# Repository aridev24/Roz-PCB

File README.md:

# Roz-PCB By AriDev24:

This is my first PCB, or you can also say my first ever hardware project that I ever made. In the beginning, I was scared to make it because it was so complex, but after some time It started to get fun. But that does not mean it got easier; it was still complex and gave me a headache. I never thought that I would be able to make a PCB as my first hardware project. 

## Features:

The following is a list of some features below: 

1. Glow-in-the-dark: whenever you take it into the darkness, the LEDs turn on, and its eyes start glowing, but in the light, the LEDs turn off.
2. You can put it in your room as a decoration so at night when you turn off the lights, it will turn on and look beautiful.
3. You can also attach it to your keychain, a great gift for a tech guy.

## Inspiration:

This PCB is highly inspired by a robot named Roz from the movie "The Wild Robot." I took a beautiful scene from the movie where the robot is holding a little duck and converted that into a PCB

## Components:
- 1x CR2032 battery holder
- 2x 5mm LED
- 2x 2N3904 NPN transistor
- 1x Photoresistor (LDR)
- 2x 470Ω resistor
- 1x 4.7kΩ resistor
- 1x 47kΩ resistor

## 3D View: 

## schematic:

## PCB:

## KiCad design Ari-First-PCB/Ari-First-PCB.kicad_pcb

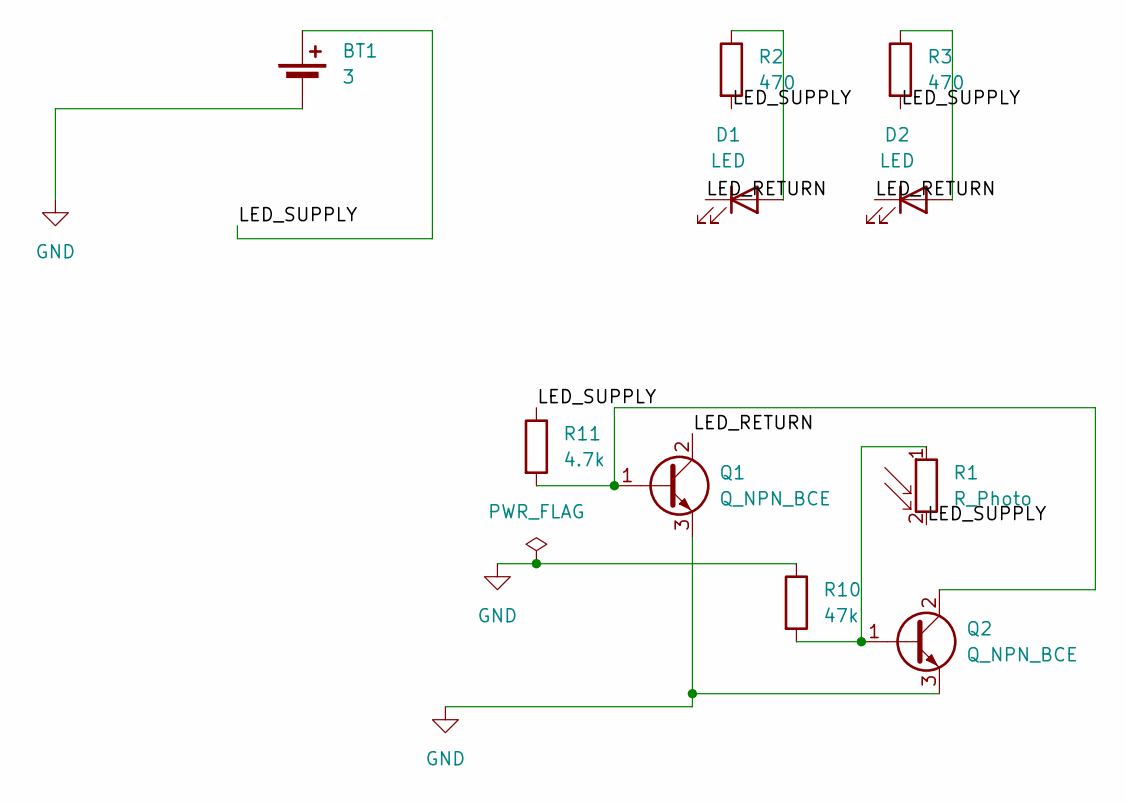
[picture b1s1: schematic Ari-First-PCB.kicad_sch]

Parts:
BT1: 3; BatteryHolder_Keystone_3034_1x20mm
D1, D2: LED; LED_D5.0mm
Q1, Q2: Q_NPN_BCE; TO-92L_HandSolder
R1: R_Photo; R_LDR_5.1x4.3mm_P3.4mm_Vertical
R2, R3: 470; R_Axial_DIN0207_L6.3mm_D2.5mm_P7.62mm_Horizontal
R10: 47k; R_Axial_DIN0207_L6.3mm_D2.5mm_P7.62mm_Horizontal
R11: 4.7k; R_Axial_DIN0207_L6.3mm_D2.5mm_P7.62mm_Horizontal

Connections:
/LED_RETURN: D1.1 (K), D2.1 (K), Q1.2 (C)
/LED_SUPPLY: BT1.1 (+), R1.2, R2.2, R3.2, R11.1
GND: BT1.2 (-), Q1.3 (E), Q2.3 (E), R10.1
unnamed: D1.2 (A), R2.1
unnamed: D2.2 (A), R3.1
unnamed: Q1.1 (B), Q2.2 (C), R11.2
unnamed: Q2.1 (B), R1.1, R10.2

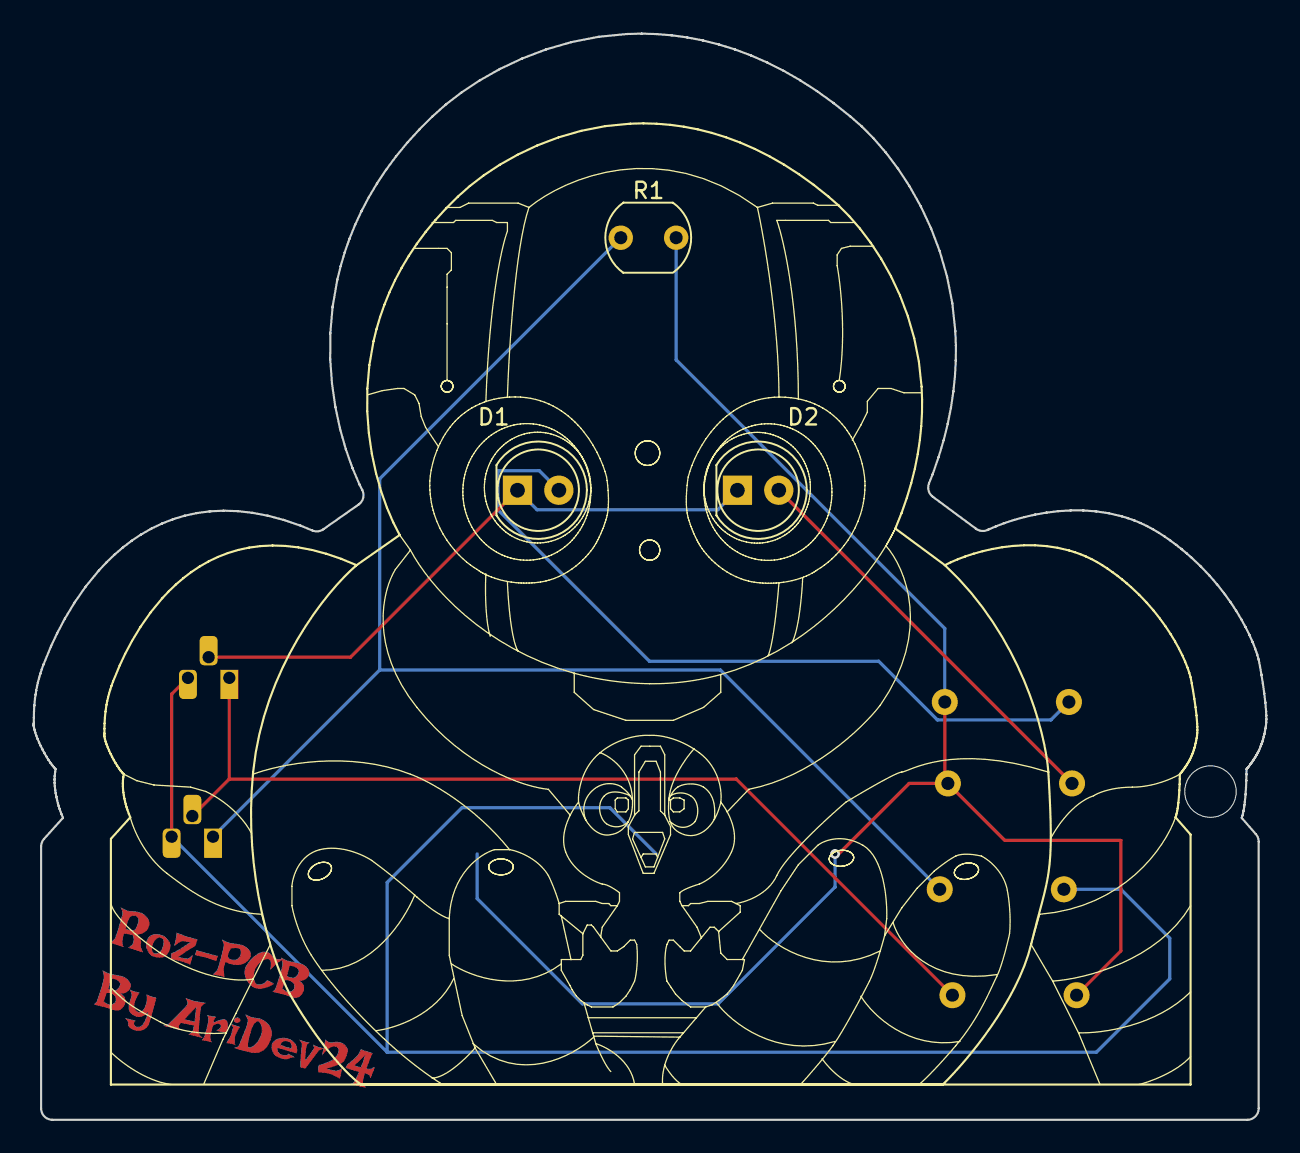
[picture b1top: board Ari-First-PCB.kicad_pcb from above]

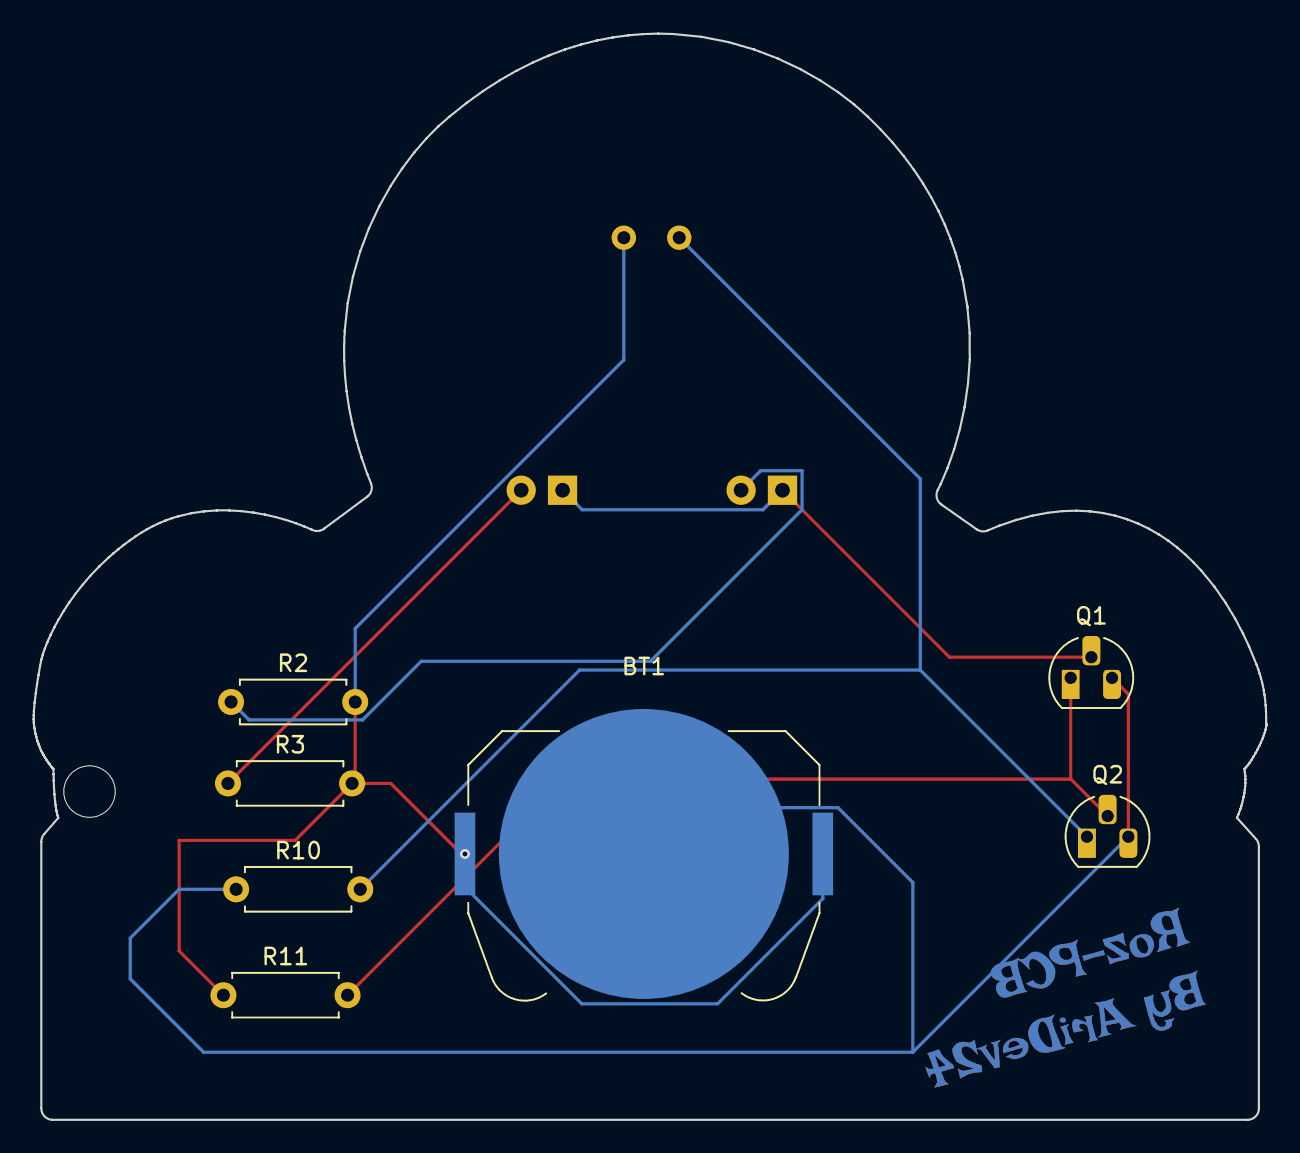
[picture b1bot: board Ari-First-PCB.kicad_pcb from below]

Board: 2 copper layers, 75.7 x 66.7 mm, 10 parts (7 on the bottom side), 7 nets.

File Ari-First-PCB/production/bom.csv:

Designator,Footprint,Quantity,Value,LCSC Part #
BT1,BatteryHolder_Keystone_3034_1x20mm,1,Battery_Cell,
"D1, D2",LED_D5.0mm,2,LED,
"Q1, Q2",TO-92L_HandSolder,2,Q_NPN_BCE,
R1,R_LDR_5.1x4.3mm_P3.4mm_Vertical,1,R_Photo,
R10,R_Axial_DIN0207_L6.3mm_D2.5mm_P7.62mm_Horizontal,1,47k,
R11,R_Axial_DIN0207_L6.3mm_D2.5mm_P7.62mm_Horizontal,1,4.7k,
"R2, R3",R_Axial_DIN0207_L6.3mm_D2.5mm_P7.62mm_Horizontal,2,470,
